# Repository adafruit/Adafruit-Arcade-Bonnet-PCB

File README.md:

## Adafruit Arcade Bonnet PCB

<a href="http://www.adafruit.com/products/3422"><br/>
Click here to purchase one from the Adafruit shop</a>

PCB files for the Adafruit Arcade Bonnet. Format is EagleCAD schematic and board layout
* http://www.adafruit.com/product/3422

### Description

Playing retro games is easy on a Raspberry Pi - and that pocket-sized computer is pretty good at it too! All you need is a little help to connect buttons and a joystick up and you can custom design your own arcade console, desktop or stand-up machine, even just a simple controller box. It makes for a fun weekend project that will last all year.

This Adafruit Arcade Bonnet is designed to make small emulator projects a little easier to build. Here's what you can look forward to!

* It is the same size as a Pi Zero, so for really compact builds, this is super small. You can also use it with a Pi 2, 3, B+ or any 2x20 connector Pi.
* It has JST sockets so you can plug in six arcade buttons easily using our quick connects.
* Header breakouts for use with both clicky-type switched joysticks and...
* Header breakout and converter for using analog-type joysticks or thumbsticks with potentiometers inside.
* A 3W digital speaker output that can drive 4-8 ohm speakers for when using with a TV output, audio-less HDMI display or PiTFT. Works even when the Pi doesn't have a headphone jack!
* Switches are all managed with an I2C-GPIO converter with interrupt out. The converter is very fast and frees up all the pins so you can use this Bonnet with a PiTFT or any other accessory/device that uses a lot of pins!

If you don't need an amplified speaker output, analog-joystick input or minimal pin usage, check out our plain-jane Retrogame tutorial which just plugs all the buttons and joysticks right into the Pi directly.

This item as sold as a mini-kit, with a Bonnet and headers that need to be soldered in to attach it to a Raspberry Pi! It only takes a few minutes but soldering iron and solder are required.

Note: The terminal block included with your product may be blue or black.

It also does not come with any of the extras, so you can choose which buttons/joysticks/speaker you want! Here is a list of the items you can use:

Joysticks:

* Small Arcade Joystick
* Mini Analog Joystick
* Assembled 2 Axis Joystick
* Analog Thumbstick
* 2 Axis Joystick
* PSP Analog Joystick
* PSP3000 Analog Joystick

To connect them, you may want some 20 x 12" Female jumper wires.

Speakers:

* 4 ohm 3 Watt speaker
* 8 ohm 1 Watt speaker
* Mono enclosed speaker
* Mini Metal speaker (may need to turn the volume down in Emulation station)
* Thin Plastic speaker (may need to turn the volume down in Emulation station)

Arcade Buttons:

* The JST connectors on the Bonnet mate perfectly with Arcade Button Quick-Connect Wire Pairs.
* Any of our Arcade buttons will work. You can use any switch you like, really – doesn't even need to be a button!
* The translucent 30mm ones work nicely with the quick-connects and are recommended!

Note: Raspberry Pi, arcade buttons, joysticks, speaker, display, and quick-connect wires are NOT included, and must be purchased separately.

Once you've picked out all your buttons and joysticks and stuff, check out our [Getting-started guide](https://learn.adafruit.com/adafruit-arcade-bonnet-for-raspberry-pi to help you get going!

### License

Adafruit invests time and resources providing this open source design, please support Adafruit and open-source hardware by purchasing products from [Adafruit](https://www.adafruit.com)!

Designed by Limor Fried/Ladyada for Adafruit Industries.

Creative Commons Attribution/Share-Alike, all text above must be included in any redistribution. See license.txt for additional details.

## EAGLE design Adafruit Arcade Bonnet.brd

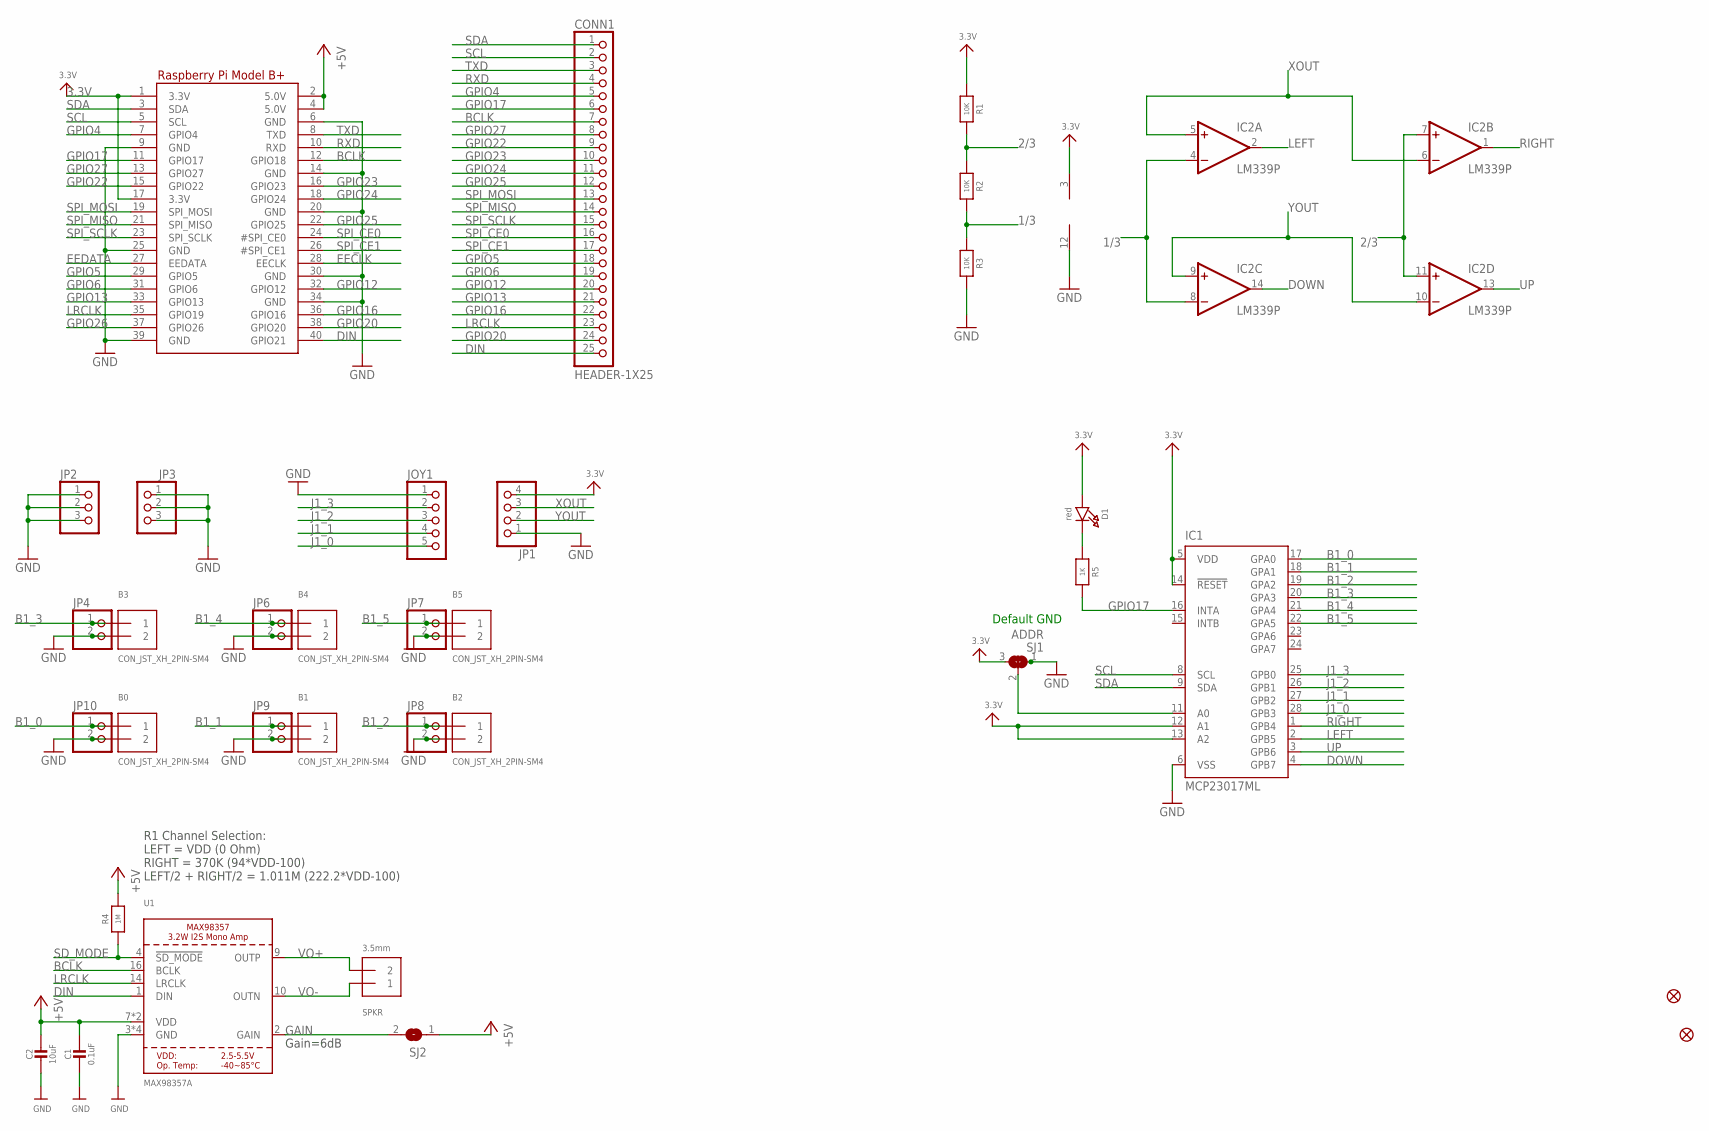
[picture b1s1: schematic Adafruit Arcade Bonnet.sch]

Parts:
B0, B1, B2, B3, B4, B5: CON_JST_XH_2PIN-SM4; JST-XH-2-SM4
C1: 0.1uF; 0603-NO
C2: 10uF; 0805-NO
CONN1: HEADER-1X25; 1X25_ROUND_70MIL
D1: red; CHIPLED_0805_NOOUTLINE
FID2, FID3: FIDUCIAL""; FIDUCIAL_1MM
IC1: MCP23017ML; QFN28-ML_6X6MM; MPN MCP23017-E/SS
IC2: LM339P; TSSOP14
JOY1: HEADER-1X5; 1X05_OVAL
JP1: HEADER-1X4; 1X04_OVAL
JP2, JP3: HEADER-1X3ROUND; 1X03_ROUND
JP4, JP6, JP7, JP8, JP9, JP10: HEADER-1X2; 1X02_OVAL
R1: 10K; 0805_10MGAP
R2, R3: 10K; 0805-NO
R4: 1M; 0603-NO
R5: 1K; 0603-NO
RPI1: RASPBERRYPI_BPLUS_PHAT; PI_BONNET
SJ1: ADDR; SOLDERJUMPER_2WAY_OPEN_NOPASTE
SJ2: SOLDERJUMPERCLOSED; SOLDERJUMPER_CLOSEDWIRE
SPKR: 3.5mm; TERMBLOCK_1X2-3.5MM
U1: MAX98357A; QFN16_3MM

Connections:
1/3: IC2.4 (-IN), IC2.8 (-IN), R2.2, R3.1
2/3: IC2.7 (+IN), IC2.11 (+IN), R1.2, R2.1
3.3V: D1.A, IC1.5 (VDD), IC1.12 (A1), IC1.13 (A2), IC1.14 (!RESET), IC2.3 (V+), JP1.4, R1.1, RPI1.1 (3.3V), RPI1.17 (3.3V), SJ1.3
+5V: C1.1, C2.1, R4.2, RPI1.2 (5.0V), RPI1.4 (5.0V), SJ2.1, U1.7 (VDD), U1.8 (VDD)
B1_0: B0.1, IC1.17 (GPA0), JP10.1
B1_1: B1.1, IC1.18 (GPA1), JP9.1
B1_2: B2.1, IC1.19 (GPA2), JP8.1
B1_3: B3.1, IC1.20 (GPA3), JP4.1
B1_4: B4.1, IC1.21 (GPA4), JP6.1
B1_5: B5.1, IC1.22 (GPA5), JP7.1
BCLK: CONN1.7, RPI1.12 (GPIO18), U1.16 (BCLK)
DIN: CONN1.25, RPI1.40 (GPIO21), U1.1 (DIN)
DOWN: IC1.4 (GPB7), IC2.14 (OUT)
EECLK: RPI1.28 (EECLK)
EEDATA: RPI1.27 (EEDATA)
GAIN: SJ2.2, U1.2 (GAIN)
GND: B0.2, B1.2, B2.2, B3.2, B4.2, B5.2, C1.2, C2.2, IC1.6 (VSS), IC2.12 (GND), JOY1.1, JP1.1, JP2.1, JP2.2, JP2.3, JP3.1, JP3.2, JP3.3, JP4.2, JP6.2, JP7.2, JP8.2, JP9.2, JP10.2, R3.2, RPI1.6 (GND), RPI1.9 (GND), RPI1.14 (GND), RPI1.20 (GND), RPI1.25 (GND), RPI1.30 (GND), RPI1.34 (GND), RPI1.39 (GND), SJ1.1, U1.3 (GND), U1.11 (GND), U1.15 (GND), U1.THERMAL (GND)
GPIO4: CONN1.5, RPI1.7 (GPIO4)
GPIO5: CONN1.18, RPI1.29 (GPIO5)
GPIO6: CONN1.19, RPI1.31 (GPIO6)
GPIO12: CONN1.20, RPI1.32 (GPIO12)
GPIO13: CONN1.21, RPI1.33 (GPIO13)
GPIO16: CONN1.22, RPI1.36 (GPIO16)
GPIO17: CONN1.6, IC1.16 (INTA), R5.2, RPI1.11 (GPIO17)
GPIO20: CONN1.24, RPI1.38 (GPIO20)
GPIO22: CONN1.9, RPI1.15 (GPIO22)
GPIO23: CONN1.10, RPI1.16 (GPIO23)
GPIO24: CONN1.11, RPI1.18 (GPIO24)
GPIO25: CONN1.12, RPI1.22 (GPIO25)
GPIO26: RPI1.37 (GPIO26)
GPIO27: CONN1.8, RPI1.13 (GPIO27)
J1_0: IC1.28 (GPB3), JOY1.5
J1_1: IC1.27 (GPB2), JOY1.4
J1_2: IC1.26 (GPB1), JOY1.3
J1_3: IC1.25 (GPB0), JOY1.2
LEFT: IC1.2 (GPB5), IC2.2 (OUT)
LRCLK: CONN1.23, RPI1.35 (GPIO19), U1.14 (LRCLK)
unnamed: IC1.11 (A0), SJ1.2
unnamed: D1.C, R5.1
RIGHT: IC1.1 (GPB4), IC2.1 (OUT)
RXD: CONN1.4, RPI1.10 (RXD)
SCL: CONN1.2, IC1.8 (SCL), RPI1.5 (SCL)
SDA: CONN1.1, IC1.9 (SDA), RPI1.3 (SDA)
SD_MODE: R4.1, U1.4 (!SD_MODE)
SPI_CE0: CONN1.16, RPI1.24 (#SPI_CE0)
SPI_CE1: CONN1.17, RPI1.26 (#SPI_CE1)
SPI_MISO: CONN1.14, RPI1.21 (SPI_MISO)
SPI_MOSI: CONN1.13, RPI1.19 (SPI_MOSI)
SPI_SCLK: CONN1.15, RPI1.23 (SPI_SCLK)
TXD: CONN1.3, RPI1.8 (TXD)
UP: IC1.3 (GPB6), IC2.13 (OUT)
VO+: SPKR.2, U1.9 (OUTP)
VO-: SPKR.1, U1.10 (OUTN)
XOUT: IC2.5 (+IN), IC2.6 (-IN), JP1.3
YOUT: IC2.9 (+IN), IC2.10 (-IN), JP1.2

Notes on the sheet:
R1 Channel Selection: LEFT = VDD (0 Ohm) RIGHT = 370K (94*VDD-100) LEFT/2 + RIGHT/2 = 1.011M (222.2*VDD-100)
Gain=6dB
Default GND

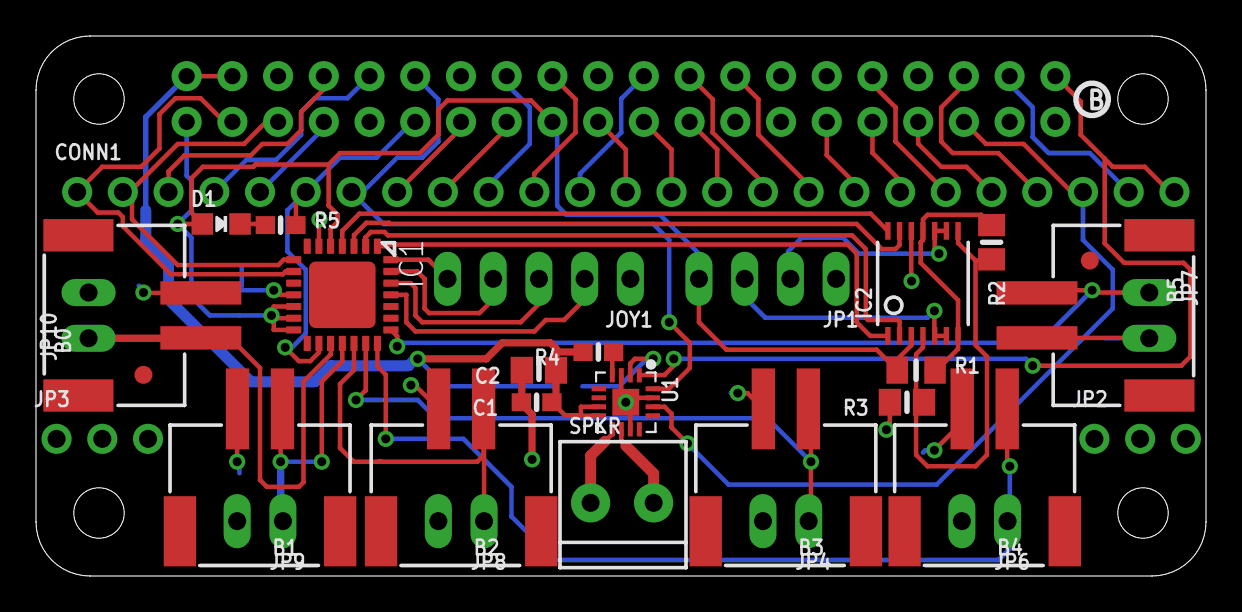
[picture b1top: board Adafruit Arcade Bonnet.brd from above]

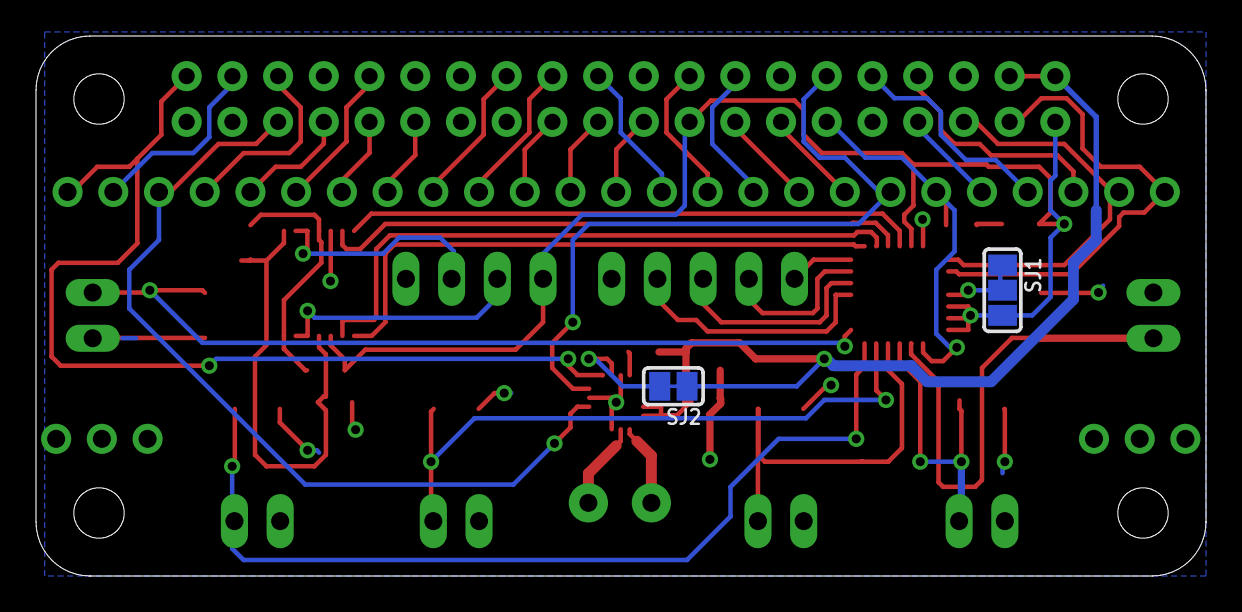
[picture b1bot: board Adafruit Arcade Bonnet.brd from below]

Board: 2 copper layers, 65.0 x 30.0 mm, 37 parts (3 on the bottom side), 52 nets.

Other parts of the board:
U$11: PCBFEAT-REV-040
U$19: BONNET_ARCADE_REVB_TOP
U$20: BONNET_ARCADE_REVB_BOT

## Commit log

2017-02-22 init
2017-02-22 url n such!

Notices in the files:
parts and their libraries:
microbuilder: This work is placed in the public domain, and may be freely used for commercial and non-commercial work with the following conditions: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
